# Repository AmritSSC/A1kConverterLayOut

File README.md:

# A1kConverterLayOut
A pcb prototype in kicad for a converter design

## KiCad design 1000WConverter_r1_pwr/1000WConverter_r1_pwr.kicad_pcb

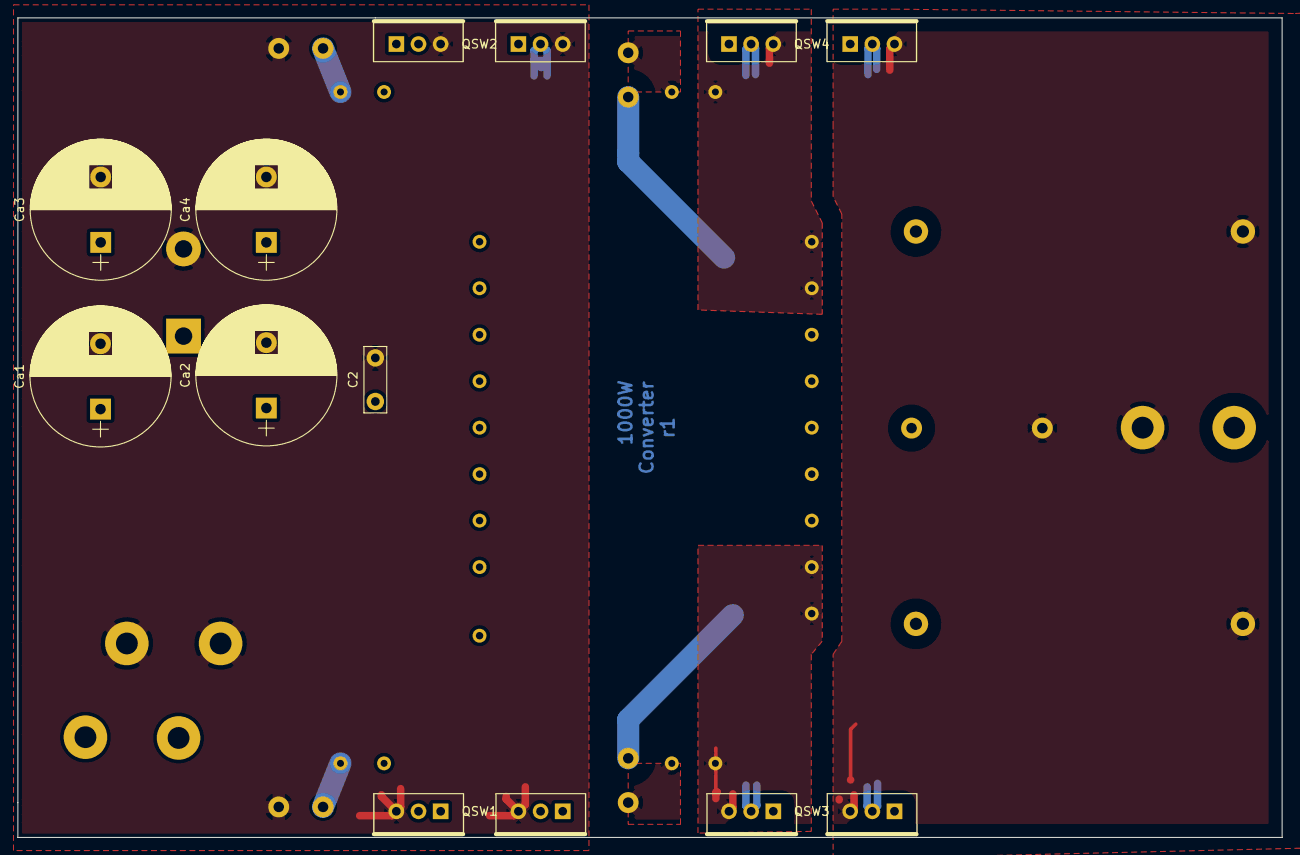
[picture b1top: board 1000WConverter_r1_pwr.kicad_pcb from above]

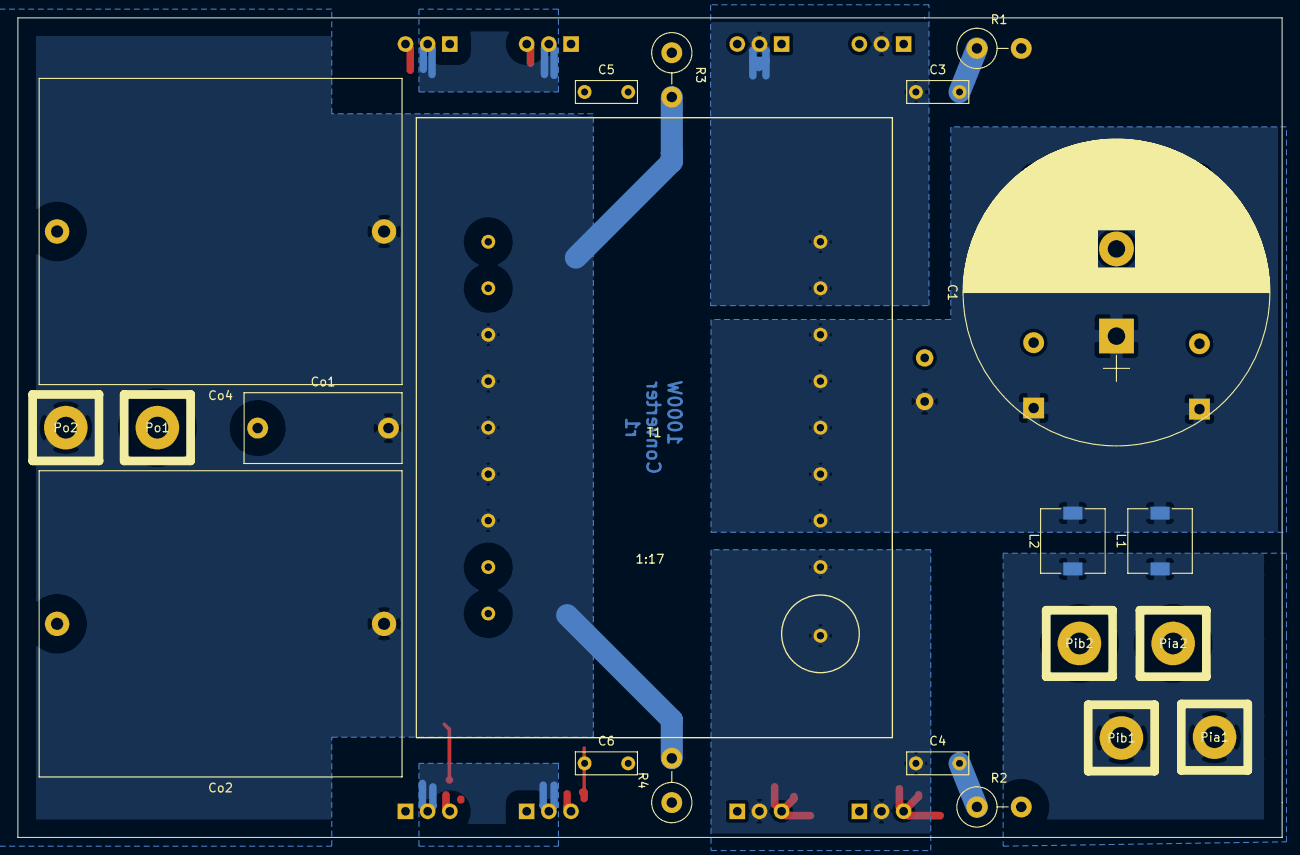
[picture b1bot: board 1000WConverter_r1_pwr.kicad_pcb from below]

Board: 4 copper layers, 145.0 x 94.0 mm, 30 parts (21 on the bottom side), 13 nets.

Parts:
C1: 12000u; CP_Radial_D35.0mm_P10.00mm_SnapIn
C2: 0.1u; C_Disc_D7.5mm_W2.5mm_P5.00mm
C3: 1n; C_Rect_L7.0mm_W2.5mm_P5.00mm
C4, C5, C6: C_Small; C_Rect_L7.0mm_W2.5mm_P5.00mm
Ca1, Ca2, Ca3, Ca4: 4000u; CP_Radial_D16.0mm_P7.50mm
Co1: 0.1u; C_Rect_L18.0mm_W8.0mm_P15.00mm_FKS3_FKP3
Co2, Co4: 50u; C_Rect_L41.5mm_W35.0mm_P37.50mm_MKS4
L1, L2: 1u; L_7.3x7.3_H4.5
Pia1, Pia2: PAD; PAD_2.5mmdrill_12Gauge
Pib1, Pib2: PAD; PAD_2.5mmdrill_12Gauge
Po1, Po2: PAD; PAD_2.5mmdrill_12Gauge
QSW1, QSW2: Parallel; TO-220_Parallel
QSW3, QSW4: TO220_comD; TO-220_ComD
R1, R2, R3, R4: 10; R_Axial_DIN0414_L11.9mm_D4.5mm_P5.08mm_Vertical
T1: TXFMR_Pushpull; TXFMR_WCM410-70pushpull

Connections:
/switches/TXi1: C4.1, QSW1.D, T1.P1
/switches/TXi2: C3.1, QSW2.D, T1.P2
/switches/TXin: C1.1, C2.1, Ca1.1, Ca2.1, Ca3.1, Ca4.1, L1.2, L2.2, T1.Pc1, T1.Pc2
GNDA: Co1.2, Co2.1, Co4.1, Po2.1, R3.2, R4.2, T1.Sc1, T1.Sc2
IN: L1.1, L2.1, Pia1.1, Pib1.1
unnamed: C3.2, R1.1
unnamed: C4.2, R2.1
unnamed: C5.2, R3.1
unnamed: C6.2, R4.1
OUT: Co1.1, Co2.2, Co4.2, Po1.1, QSW3.Sa, QSW4.Sb
S1: C1.2, C2.2, Ca1.2, Ca2.2, Ca3.2, Ca4.2, Pia2.1, Pib2.1, QSW1.S, QSW2.S, R1.2, R2.2
TXo1: C6.1, QSW3.Sb, T1.S1
TXo2: C5.1, QSW4.Sa, T1.S2

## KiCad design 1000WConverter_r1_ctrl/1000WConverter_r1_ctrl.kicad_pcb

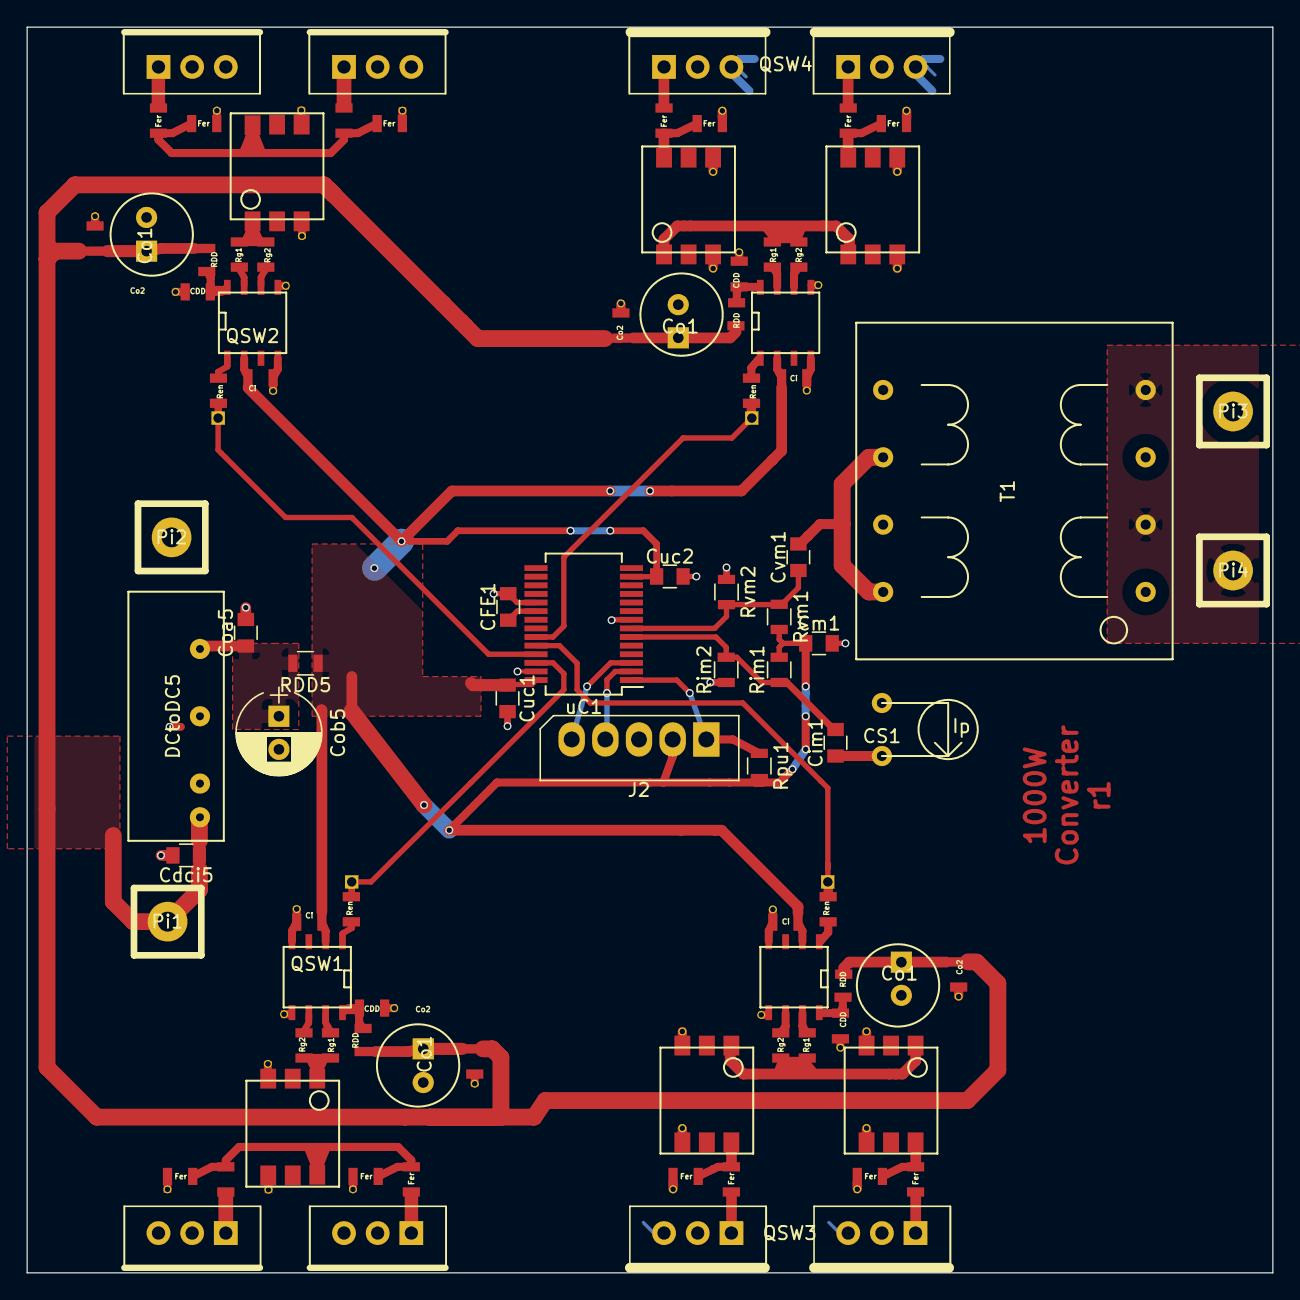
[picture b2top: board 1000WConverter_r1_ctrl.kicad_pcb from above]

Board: 4 copper layers, 94.0 x 94.0 mm, 28 parts (0 on the bottom side), 18 nets.

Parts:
CFE1: 10uF; C_0805
CS1: Current_txfmr; CS_txfmr_AZ-500
Cdci5: 0.1uF; C_0805
Cim1: 10uF; C_0805
Cm1: 10uF; C_0805
Coa5: 0.1uF; C_0805
Cob5: 100uF; CP_Radial_D6.3mm_P2.50mm
Cuc1, Cuc2: 0.1uF; C_0805
Cvm1: 10uF; C_0805
DCtoDC5: DCDC; CUI-DCDC
J2: Conn_01x05_Male; Molex_SPOX-5267_22-03-5055_05x2.54mm_Straight
Pi1, Pi2, Pi3, Pi4: PAD; PAD_1.5mmdrill
QSW1: GateDriver_Parallel; SWTO220-ParallelTXGate_connected
QSW2: GateDrive_Parallel; SWTO220-ParallelTXGate_connected
QSW3, QSW4: GateDrive_ComD; SWTO220-ComDTXGate_connected
RDD5: 10; R_0805
Rim1, Rim2: 100k; R_0805
Rpu1: 10k; R_0805
Rvm1, Rvm2: 100k; R_0805
T1: TXFMR_Pushpull; TXFMR_160D10
uC1: dsPIC33FJ12MC202; SSOP-28_5.3x10.2mm_P0.65mm

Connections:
!MCLR: J2.1, Rpu1.1, uC1.1
GND: CFE1.2, CS1.1, Cdci5.2, Cm1.2, Coa5.2, Cob5.2, Cuc1.2, Cuc2.2, DCtoDC5.-Vi, DCtoDC5.-Vo, J2.3, Pi2.1, QSW1.GNDi, QSW1.S, QSW2.GNDi, QSW2.S, QSW3.GNDi, QSW4.GNDi, Rim2.1, Rvm2.1, T1.S2, T1.Sc1, uC1.8, uC1.19, uC1.27
GNDA: Pi4.1, T1.P2, T1.Pc1
IN: Cdci5.1, DCtoDC5.+Vi, Pi1.1, QSW1.+Vo, QSW2.+Vo, QSW3.+Vo, QSW4.+Vo
Ioutmeas: Cim1.2, Rim1.1, Rim2.2, uC1.6
unnamed: CFE1.1, uC1.20
unnamed: CS1.2, Cim1.1
unnamed: Coa5.1, Cob5.1, DCtoDC5.+Vo, RDD5.2
unnamed: Cvm1.2, T1.S1, T1.Sc2
OUT: Pi3.1, QSW3.Sa, QSW4.Sb, T1.P1, T1.Pc2
PGEC2: J2.5, uC1.3
PGED2: J2.4, uC1.2
VDDI: Cm1.1, Cuc1.1, Cuc2.1, J2.2, QSW1.VDDi, QSW2.VDDi, QSW3.VDDi, QSW4.VDDi, RDD5.1, Rim1.2, Rpu1.2, Rvm1.2, uC1.13, uC1.28
VI1: QSW1.Vsig, uC1.26
VI2: QSW2.Vsig, uC1.25
VI3: QSW3.Vsig, uC1.24
VI4: QSW4.Vsig, uC1.23
Voutmeas: Cvm1.1, Rvm1.1, Rvm2.2, uC1.7

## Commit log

2019-07-18 Initial Prototype versions-
